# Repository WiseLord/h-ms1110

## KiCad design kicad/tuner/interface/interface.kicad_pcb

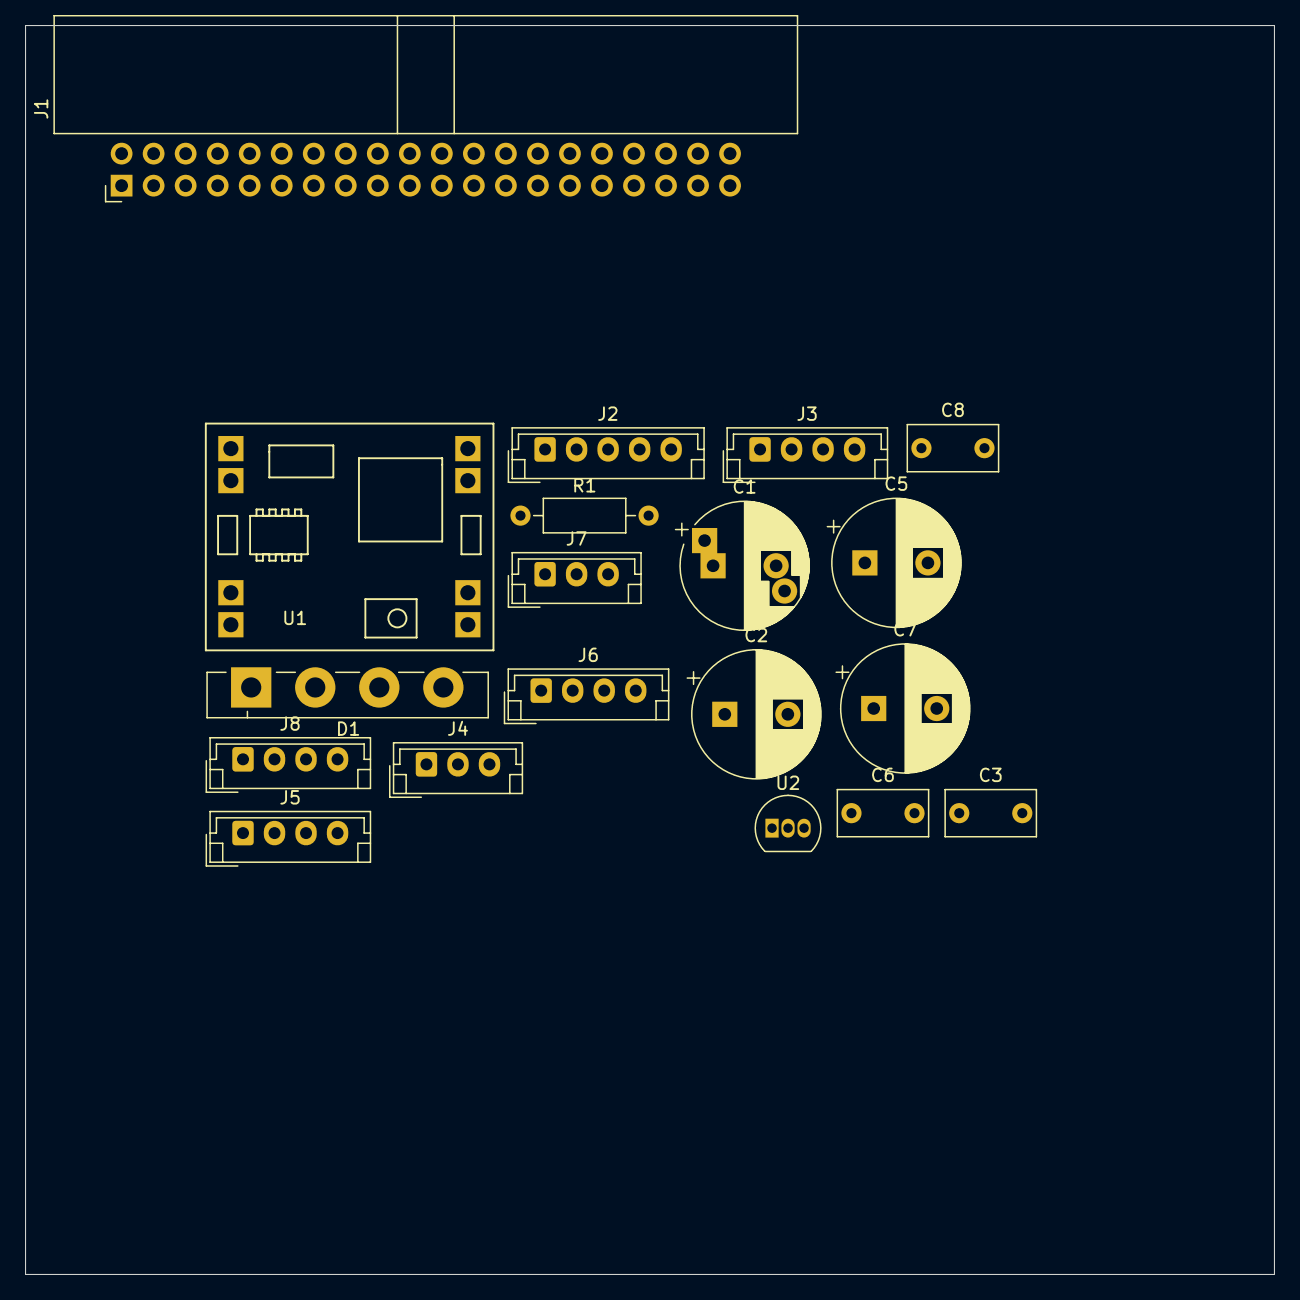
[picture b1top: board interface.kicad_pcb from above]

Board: 2 copper layers, 99.1 x 99.1 mm, 19 parts (0 on the bottom side), 22 nets, no tracks yet.

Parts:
C1: 1000.0; CP_Radial_D10.0mm_P5.00mm_P7.50mm
C2: 470.0; CP_Radial_D10.0mm_P5.00mm
C3, C6, C8: 0.1; C_Rect_L7.0mm_W3.5mm_P5.00mm
C5, C7: 220.0; CP_Radial_D10.0mm_P5.00mm
D1: GBU8K; Diode_Bridge_Vishay_GBU
J1: H-MS1110_Bus; IDC-Header_2x20_P2.54mm_Horizontal
J2: EXT_INPUT; JST_EH_B5B-EH-A_1x05_P2.50mm_Vertical
J3: SYNC; JST_EH_B4B-EH-A_1x04_P2.50mm_Vertical
J4: ROT; JST_EH_B3B-EH-A_1x03_P2.50mm_Vertical
J5: CONTROL; JST_EH_B4B-EH-A_1x04_P2.50mm_Vertical
J6: FP_POWER; JST_EH_B4B-EH-A_1x04_P2.50mm_Vertical
J7: SPECT; JST_EH_B3B-EH-A_1x03_P2.50mm_Vertical
J8: I2C; JST_EH_B4B-EH-A_1x04_P2.50mm_Vertical
R1: 100; R_Axial_DIN0207_L6.3mm_D2.5mm_P10.16mm_Horizontal
U1: MP1584EN_module
U2: L78L12_TO92; TO-92_Inline

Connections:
+5V: C2.1, C3.1, J6.1, J6.2, U1.7, U1.8
/+3.3VA: J1.9, J2.1
/AC1: D1.3, J1.17
/AC2: D1.2, J1.19
/AD1: J1.2, J2.3
/AD2: J1.1, J2.2
/AD3: J1.14, J2.4
/MUTE: J1.24, J5.1
/REMOTE: J1.15, J5.3
/ROT-A: J1.12, J4.3
/ROT-B: J1.10, J4.1
/SP_L: J1.27, J7.1
/SP_R: J1.34, J7.3
/STBY: J1.22, J5.2
/SYNC_DATA: J1.16, J3.2
/SYNC_SCK: J1.18, J3.3
GNDA: C5.2, C6.2, C7.2, C8.2, J1.25, J1.33, J1.35, J1.38, U2.2
GNDD: C1.2, C2.2, C3.2, D1.4, J1.11, J2.5, J3.4, J4.2, J5.4, J6.3, J6.4, J7.2, J8.4, U1.3, U1.4, U1.5, U1.6
unnamed: C1.1, D1.1, U1.1, U1.2
unnamed: C5.1, C6.1, R1.1, U2.3
unnamed: C7.1, C8.1, U2.1
unnamed: J1.32, R1.2

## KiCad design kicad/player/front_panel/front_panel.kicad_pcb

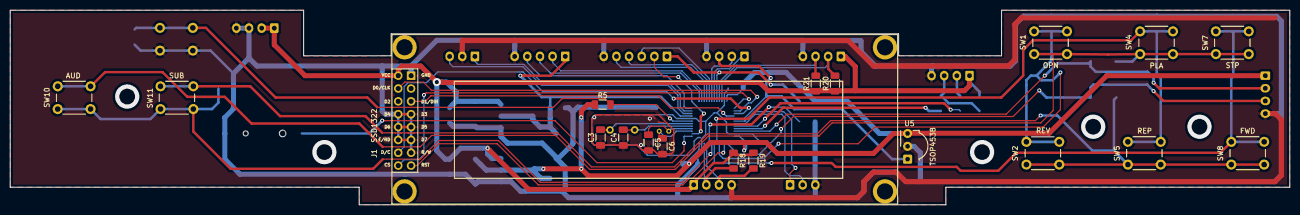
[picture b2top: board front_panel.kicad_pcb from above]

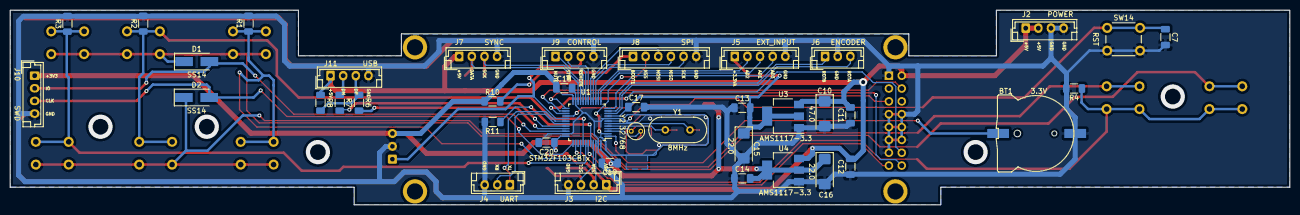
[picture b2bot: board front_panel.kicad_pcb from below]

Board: 2 copper layers, 253.0 x 38.5 mm, 59 parts (40 on the bottom side), 47 nets.

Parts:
BT1: 3.3V; CR1220
C3, C4: 20p; C_1206_3216Metric_Pad1.33x1.80mm_HandSolder
C5, C6: 6p2; C_1206_3216Metric_Pad1.33x1.80mm_HandSolder
C7: 100n; C_1206_3216Metric_Pad1.33x1.80mm_HandSolder
C10: 47.0; CP_EIA-6032-28_Kemet-C
C11, C12, C13, C14, C17, C18, C19, C20: 0.1; C_1206_3216Metric_Pad1.33x1.80mm_HandSolder
C15, C16: 22.0; CP_EIA-6032-28_Kemet-C
D1, D2: SS14; D_SMA_Handsoldering
J1: SSD1322; SSD1322_3.12
J2: POWER; JST_EH_B4B-EH-A_1x04_P2.50mm_Vertical
J3: I2C; JST_EH_B4B-EH-A_1x04_P2.50mm_Vertical
J4: UART; JST_EH_B3B-EH-A_1x03_P2.50mm_Vertical
J5: EXT_INPUT; JST_EH_B5B-EH-A_1x05_P2.50mm_Vertical
J6: ENCODER; JST_EH_B3B-EH-A_1x03_P2.50mm_Vertical
J7: SYNC; JST_EH_B4B-EH-A_1x04_P2.50mm_Vertical
J8: SPI; JST_EH_B6B-EH-A_1x06_P2.50mm_Vertical
J9: CONTROL; JST_EH_B4B-EH-A_1x04_P2.50mm_Vertical
J10: SWD; JST_EH_B4B-EH-A_1x04_P2.50mm_Vertical
J11: USB; JST_EH_B4B-EH-A_1x04_P2.50mm_Vertical
R1, R2, R3, R4: 33k; R_1206_3216Metric_Pad1.30x1.75mm_HandSolder
R5: 22k; R_1206_3216Metric_Pad1.30x1.75mm_HandSolder
R6, R7: 22; R_1206_3216Metric_Pad1.30x1.75mm_HandSolder
R8, R18, R19, R20, R21: 10k; R_1206_3216Metric_Pad1.30x1.75mm_HandSolder
R10, R11: 100k; R_1206_3216Metric_Pad1.30x1.75mm_HandSolder
SW1: OPN; SW_PUSH_6mm
SW2: REV; SW_PUSH_6mm
SW4: PLA; SW_PUSH_6mm
SW5: REP; SW_PUSH_6mm
SW7: STP; SW_PUSH_6mm
SW8: FWD; SW_PUSH_6mm
SW10: AUD; SW_PUSH_6mm
SW11: SUB; SW_PUSH_6mm
SW14: RST; SW_PUSH_6mm
U1: STM32F103CBTx; LQFP-48_7x7mm_P0.5mm
U3, U4: AMS1117-3.3; SOT-223-3_TabPin2
U5: TSOP4538; Vishay_MOLD-3Pin
Y1: 8MHz; Crystal_HC49-4H_Vertical
Y2: 32768; Crystal_C38-LF_D3.0mm_L8.0mm_Vertical

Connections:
+3.3VA: C13.2, C15.1, C17.1, J5.1, U1.9, U3.2
+3V3: C14.2, C16.1, C18.1, C19.1, C20.1, J10.1, R5.1, R10.1, U1.24, U1.36, U1.48, U4.2, U5.3
+5V: C10.1, C11.2, C12.2, J1.2, J2.1, J2.2, J3.1, J7.1, J11.1, R8.1, R18.1, R19.1, R20.1, R21.1, U3.3, U4.3
/AD1: J5.3, U1.13
/AD2: J5.2, U1.14
/AD3: J5.4, U1.12
/BOOT0: R11.1, U1.44
/BOOT1: J8.1, R10.2, U1.20
/DISP_CLK: J1.4, U1.26
/DISP_CS: J1.16, U1.25
/DISP_DC: J1.14, U1.27
/DISP_DIN: J1.5, U1.28
/DISP_RST: J1.15, U1.38
/DM: J11.2, R7.1
/DP: J11.3, R6.1, R8.2
/K1: R1.1, SW1.1, SW2.1, U1.40
/K2: R2.1, SW4.1, SW5.1, U1.41
/K3: R3.1, SW7.1, SW8.1, U1.42
/K4: R4.1, SW10.1, SW11.1, U1.43
/KS1: D1.1, SW1.2, SW4.2, SW7.2, SW10.2
/KS2: D2.1, SW2.2, SW5.2, SW8.2, SW11.2
/MUTE: J9.1, U1.19
/NRST: C7.1, R5.2, SW14.1, U1.7
/OSC32_IN: C6.1, U1.3, Y2.2
/OSC32_OUT: C5.1, U1.4, Y2.1
/OSC_IN: C4.2, U1.5, Y1.1
/OSC_OUT: C3.2, U1.6, Y1.2
/REMOTE: J9.3, U1.29, U5.1
/ROTA: J6.3, U1.10
/ROTB: J6.1, U1.11
/RX: J4.2, U1.31
/S1: D1.2, J10.2, U1.34
/S2: D2.2, J10.3, U1.37
/SCL: J3.3, R19.2, U1.45
/SDA: J3.2, R18.2, U1.46
/SPI_MISO: J8.4, U1.16
/SPI_MOSI: J8.3, U1.17
/SPI_NSS: J8.2, U1.2
/SPI_SCK: J8.5, U1.15
/STBY: J9.2, U1.18
/SYNC_DATA: J7.2, R20.2, U1.22
/SYNC_SCK: J7.3, R21.2, U1.21
/TX: J4.1, U1.30
/USB_DM: R7.2, U1.32
/USB_DP: R6.2, U1.33
/VBAT: BT1.1, U1.1
GNDD: BT1.2, C3.1, C4.1, C5.2, C6.2, C7.2, C10.2, C11.1, C12.1, C13.1, C14.1, C15.2, C16.2, C17.2, C18.2, C19.2, C20.2, J1.1, J1.7, J1.8, J1.9, J1.10, J1.11, J1.12, J1.13, J2.3, J2.4, J3.4, J4.3, J5.5, J6.2, J7.4, J8.6, J9.4, J10.4, J11.4, R1.2, R2.2, R3.2, R4.2, R11.2, SW14.2, U1.8, U1.23, U1.35, U1.47, U3.1, U4.1, U5.2

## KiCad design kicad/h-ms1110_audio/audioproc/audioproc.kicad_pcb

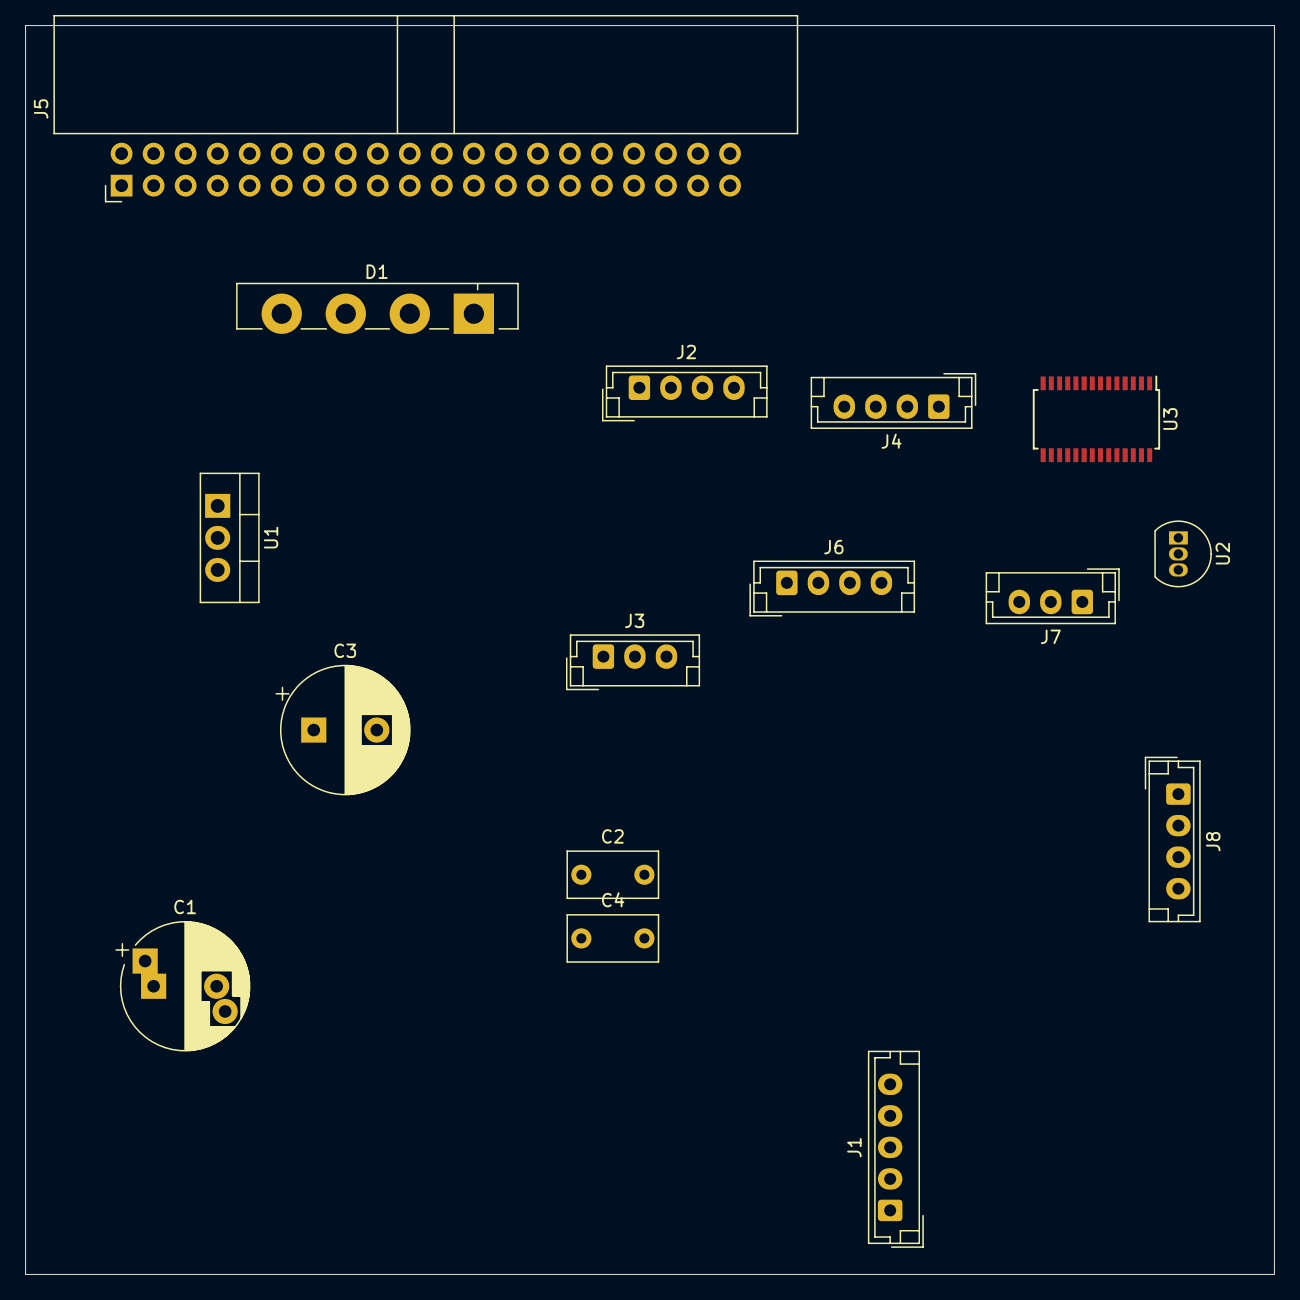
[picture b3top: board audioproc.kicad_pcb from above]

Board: 2 copper layers, 99.1 x 99.1 mm, 16 parts (0 on the bottom side), 27 nets, no tracks yet.

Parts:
C1: 4700.0; CP_Radial_D10.0mm_P5.00mm_P7.50mm
C2, C4: 0.1; C_Rect_L7.0mm_W3.5mm_P5.00mm
C3: 1000.0; CP_Radial_D10.0mm_P5.00mm
D1: GBU8K; Diode_Bridge_Vishay_GBU
J1: EXT_INPUT; JST_EH_B5B-EH-A_1x05_P2.50mm_Vertical
J2: SYNC; JST_EH_B4B-EH-A_1x04_P2.50mm_Vertical
J3: ROT; JST_EH_B3B-EH-A_1x03_P2.50mm_Vertical
J4: CONTROL; JST_EH_B4B-EH-A_1x04_P2.50mm_Vertical
J5: H-MS1110_Bus; IDC-Header_2x20_P2.54mm_Horizontal
J6: FP_POWER; JST_EH_B4B-EH-A_1x04_P2.50mm_Vertical
J7: AUDIO; JST_EH_B3B-EH-A_1x03_P2.50mm_Vertical
J8: I2C; JST_EH_B4B-EH-A_1x04_P2.50mm_Vertical
U1: LM7805_TO220; TO-220-3_Vertical
U2: L78L12_TO92; TO-92_Inline
U3: TDA7719; TSSOP-28_4.4x9.7mm_P0.65mm

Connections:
+5V: C3.1, C4.1, J6.1, J6.2, U1.3
/+3.3VA: J1.1, J5.9
/AC1: D1.3, J5.17
/AC2: D1.2, J5.19
/AD1: J1.3, J5.2
/AD2: J1.2, J5.1
/AD3: J1.4, J5.14
/MUTE: J4.1, J5.24
/OUT_L: J5.29, U3.21
/OUT_R: J5.30, U3.18
/REMOTE: J4.3, J5.15
/ROT-A: J3.3, J5.12
/ROT-B: J3.1, J5.10
/SCL: J8.3, U3.25
/SDA: J8.2, U3.26
/SP_L: J5.27, J7.1, U3.17
/SP_R: J5.34, J7.3, U3.16
/STBY: J4.2, J5.22
/SYNC_DATA: J2.2, J5.16
/SYNC_SCK: J2.3, J5.18
/TUN-L: J5.39, U3.1
/TUN-R: J5.40, U3.2
GNDA: J5.25, J5.33, J5.35, J5.38, U2.2, U3.15
GNDD: C1.2, C2.2, C3.2, C4.2, D1.4, J1.5, J2.4, J3.2, J4.4, J5.11, J6.3, J6.4, J7.2, J8.4, U1.2
unnamed: C1.1, C2.1, D1.1, U1.1
unnamed: J5.32, U2.3
unnamed: U2.1, U3.24

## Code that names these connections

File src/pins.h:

#ifndef PINS_H
#define PINS_H

#ifdef __cplusplus
extern "C" {
#endif

#include <stdbool.h>
#include <stdint.h>

#include "hwlibs.h"

#define CONCAT(x,y)             x ## y

#define SET(p)                  (LL_GPIO_SetOutputPin(CONCAT(p, _Port), CONCAT(p, _Pin)))
#define CLR(p)                  (LL_GPIO_ResetOutputPin(CONCAT(p, _Port), CONCAT(p, _Pin)))

#define READ(p)                 (LL_GPIO_ReadInputPort(CONCAT(p, _Port)) & (CONCAT(p, _Pin) >> GPIO_PIN_MASK_POS) & 0x0000FFFFU)

// TFT parallel (8-bit) wiring
#define DISP_CS_Port            GPIOB
#define DISP_CS_Pin             LL_GPIO_PIN_12
#define DISP_RS_Port            GPIOB
#define DISP_RS_Pin             LL_GPIO_PIN_14  // SPI DC
#define DISP_RST_Port           GPIOA
#define DISP_RST_Pin            LL_GPIO_PIN_15

#define STBY_Port               GPIOB
#define STBY_Pin                LL_GPIO_PIN_0
#define MUTE_Port               GPIOB
#define MUTE_Pin                LL_GPIO_PIN_1

#define AIN_BTN_Port            GPIOA
#define AIN_BTN_Pin             LL_GPIO_PIN_4
#define AIN_BTN_ADC_Channel     LL_ADC_CHANNEL_4
#define AIN_POT_A_Port          GPIOA
#define AIN_POT_A_Pin           LL_GPIO_PIN_2
#define AIN_POT_A_Channel       LL_ADC_CHANNEL_2
#define AIN_POT_B_Port          GPIOA
#define AIN_POT_B_Pin           LL_GPIO_PIN_3
#define AIN_POT_B_Channel       LL_ADC_CHANNEL_3

#define ENCODER_Port            GPIOA
#define ENCODER_A_Pin           LL_GPIO_PIN_11
#define ENCODER_B_Pin           LL_GPIO_PIN_12

// Remote control pins
#define RC_Port                 GPIOA
#define RC_Pin                  LL_GPIO_PIN_8
#define RC_ExtiLine             LL_EXTI_LINE_8
#define RC_AR_ExtiPort          LL_GPIO_AF_EXTI_PORTA
#define RC_AR_ExtiLine          LL_GPIO_AF_EXTI_LINE8

void pinsInit(void);

#ifdef __cplusplus
}
#endif

#endif // PINS_H

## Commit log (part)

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2019-12-10 Schematic and initial PCB
2019-12-11 Initial SSD1322-ready code based on wl_lcd-f103
2019-12-11 Basic analog input reading
2019-12-14 KiCad: Move front_panel project to subdir
2019-12-15 Remove unused stuff
2019-12-15 Use colors of 4-bit grayscale
2019-12-15 Sync graphic library with ampcontrol/wl_lcd
2019-12-17 Use memory functions from stdlib
2020-01-07 Sync with ampcontrol-f103
2020-01-07 Improve SSD1322 code
2020-01-07 SSD1322 rotate support
2020-01-08 Add base amp file
2020-01-08 Basic drawing skeleton
2020-01-08 Input timer
2020-01-08 Draw pot values
2020-01-10 Move potentiometer calculations to input module
2020-01-10 Fixes for potentiometer calculations
2020-01-11 Sync code with other projects
2020-01-11 Add analog buttons support
2020-01-11 Added some code from ampcontrol project
2020-01-11 Basic ON/OFF control
2020-01-12 Separate screen module
2020-01-12 Change to STM32F103CB in Kicad project
2020-01-12 Fix analog buttons
2020-01-12 Rotary encoder support
2020-01-16 Cleanum makefile
2020-01-17 Add basic schematic for audioproc module
2020-01-18 Basic audio support
2020-01-18 Basic input indication
2020-01-19 Small rework of audio API
2020-01-19 Rid potentiometer grid from audio params
2020-01-19 Sync audio code with ampcontrol
2020-01-19 Improve potentiometer accuracy
2020-01-19 Control bass/treble via potentiometers
2020-01-19 Add menu files
2020-01-19 Basic menu drawing
2020-01-20 Layout and palette support from ampcontrol
2020-01-20 Improve handling potentiometers
2020-01-21 Schematics update
2020-01-21 Basic menu navigation
2020-01-23 Remote control support
2020-01-25 Audioproc schematic update
2020-02-01 Refactored colors
2020-02-02 Add handler for USART1 interrupt
2020-02-25 Fix flash definitions
2020-03-08 Matrix keyboard support
2020-03-08 Enable SWD interface in standby mode
2020-03-09 Spectrum draft from ampcontrol project
2020-03-09 Update schematcis and PCB
2020-03-10 Some work on spectrum settings
2020-03-10 LTO support, currently disabled
2020-03-11 Draw time
2020-03-14 Sync spectrum code with ampcontrol
2020-03-14 Move project files outside src directory
2020-03-14 Reset silence timer on signal
2020-03-14 Reduce display current
2020-03-14 Small fix in sch
2020-03-14 Remove junk SSD1322 scroll defines
2020-03-18 Split audio and tuner code
2020-03-21 Sync and cleanup audio code
2020-03-21 Move audio and tuner code to common dir
2020-03-22 Pass STANDBY to tuner
2020-03-22 Introduce sync structures
2020-03-22 Pass actions from tuner to audio
2020-03-22 Common input module for both audio and tuner
2020-03-23 Use common layout for tuner and audio
2020-03-23 Common canvas for both audio and tuner
2020-03-24 Refactor showStandby
2020-03-24 Adjust some SSD1322 brightness-related params
2020-03-25 Fix spectrum drawing
2020-03-25 Separate schematic for audio and tuner front panels
2020-03-27 Update audioproc schematic
2020-03-28 Add MP1584 module symbols
2020-03-28 Add player block schematics
2020-04-02 Bigger fonts for date and time
2020-04-04 Remove separate canvases
2020-04-04 Separate matrix input library
2020-04-04 Separate analog input library
2020-04-05 Rework player schematics
2020-04-06 Player board skeleton
2020-04-08 Player board: mcu part
2020-04-08 Autorouted player front panel PCB
2020-04-19 Finished player board
2020-04-23 Some simplifications in canvas
2020-04-23 Separate spectrum drawing
2020-04-23 Change sp defaul settings
2020-04-24 Refactor spectrum view
2020-04-24 Simplify layout
2020-04-24 Refactored widgets, added paramview one
2020-04-26 Refactored tune
2020-04-26 Refactored screen
2020-04-26 Refactored amp
2020-04-26 Refactor project files
2020-04-26 Refactored palette
2020-04-26 Refactor actions
2020-04-26 Draw volume progressbar
2020-04-27 Show current input
2020-04-27 Handling analog input
2020-04-28 Separate project files
2020-04-28 Refactor eemul and settings
2020-04-28 Map display buttons
2020-04-28 Pass all buttons from tuner
2020-04-28 Rework pass buttons and encoder
2020-04-28 Sync time
2020-04-29 Date and time screens
2020-04-30 Fix volume restoring
2020-04-30 Sync with ampcontrol project
2020-04-30 Add setup action and screen skeleton
2020-05-01 Remove layout
2020-05-02 Refactored screens
2020-05-02 Proper SWD handling
2020-05-02 Date/time setup implemented
2020-05-02 Get rid of utilMkStr()
2020-05-02 Add time and date views
2020-05-02 Remove MUTE/STBY in tuner
2020-05-02 Some fixes
2020-05-03 Implement alarm setup
2020-05-03 Remote setup
2020-05-03 Fix setup navigation
2020-05-04 Sync spectrum mode
2020-05-05 Rename KiCad projects
2020-05-05 Add useconds delay function
2020-05-05 Add tuner interface board skeleton
2020-05-09 Initial LC7213X PLL support
2020-05-10 Basic FM screen
2020-05-10 Basic radio tuning
2020-05-11 Fix tuner freq after power off
2020-05-11 Add registers for LC7213X
2020-05-11 LC7213X improvements
2020-05-17 Rework pins
2020-05-29 Prepare slave data to transmit earlier
2020-05-29 Rework and optimize master-to-slave sync
2020-05-29 Rework and optimize slave-to-master sync
2020-05-30 Sync display code with ampcontrol
2020-06-06 Add player subproject
2020-06-06 Rework some sync structs
2020-06-06 Sync player support
2020-07-09 Weekday draw in player module
2020-08-20 Rework audio module to be main block
2020-08-21 Rename projects
2020-08-21 Show spectrum in spectrum module
2020-08-22 Fix tuneview in player
2020-09-06 Sync display code
2020-09-13 Sync with latest GLCD library
2020-09-13 Small refactoring
2020-09-14 Refactor inType
2020-09-15 Refactor handle SWD function
2020-09-17 Amp struct unification
2020-09-17 Fix unused input label
2020-09-17 Fix input screen timeout
2020-09-22 Rearrange actions and make remote volume buttons work
2020-09-22 Audio mute support. Screen implementation required
2020-11-01 Refactored project
2020-11-01 Station storing
2020-11-03 Added fav stations support
2020-11-08 Support station detect
2020-11-12 Draw PT2579 tuner schematic part
2020-11-16 Update interfaces schematics
2020-11-18 Enable TDA7719 subwoofer channels
2020-11-18 Make TDA7719 able to use 2.0, 2.1, 4.0, 4.1 modes
2020-11-18 Function to check for supported audio mode
2020-11-18 Enable LP filter in sub modes for TDA7719
2020-11-20 Improve subwoofer gain on TDA7719
2020-12-03 Basic work with mpd-uart.py
2020-12-03 Rename audio inputs
2020-12-03 Better MPD control
2020-12-03 mpd-uart systemd service
2020-12-03 Fix crash
2020-12-04 Icons support
2020-12-04 Update MPD icon
2020-12-04 Elapsed time periodic passing
2020-12-04 Scroll song name support
2020-12-05 Increase MPD drawing performance
2020-12-05 Add play/pause/stop icons support
2020-12-05 Update schematics
2020-12-06 MPC: add more status icons
2020-12-06 Add MPD status control
2020-12-06 Project refactoring
2020-12-07 Add InputView
2020-12-07 Add AUX icons
2020-12-07 Update mpd-uart scripts
2020-12-07 Small input refactoring
2020-12-07 Refactored input actions
2020-12-07 Small handlers refactoring
2020-12-07 Refactored settings
2020-12-07 Fix broken RC and tuner
2020-12-07 Add more RC buttons to recognize
2020-12-08 Sync refactoring
2020-12-08 Basic tuner sync
2020-12-08 More tuner sync parameters
2020-12-08 Request tuner on player start
2020-12-08 Add tuner icons
2020-12-09 Refactored projects
2020-12-09 Common amp file
2020-12-09 Get buttons and encoders in common amp
2020-12-11 Fix build error if LC7213X is not selected
2020-12-12 Sync tuner code with ampcontrol
2020-12-13 Refactored tuner parser
2020-12-13 Simple RDS demod implementation
2020-12-13 RDS demod through buffer with correction
2020-12-18 Update player schematcis
2020-12-18 IconImage widget
2020-12-19 Refactored widgets
2020-12-19 Add scrolltext widget
2020-12-19 Use TunerView to draw radio
2020-12-19 Refactoring tunerView
2020-12-19 Refactored player positioning
2020-12-19 Sync RDS
2020-12-19 Add SPDIF icon
2020-12-20 RDS flag handling in tuner
2020-12-20 Simplify RDS sync
2020-12-20 RDS lost handling
2020-12-21 Stations store/clear support
2020-12-22 Draw station num
2020-12-23 Use tuner encoder as REW/FFWD in MPD
2020-12-24 Refactoring amp
2020-12-24 Improve RDS parser
2021-01-29 Sync MPC module with ampcontrol
2021-01-29 Don't sync with slaves if they are not online
2021-01-30 Support brightnes control for SSD1322
2021-01-30 Reworking time output
2021-01-30 Common project for all modules
2021-01-30 Combine project files
2021-01-30 Rework sp modes, add peaks toggle button
2021-01-31 Remove ssd1322.h
2021-01-31 SSD1322 init rework
2021-01-31 Demo screensaver support
2021-01-31 Refactored demo into starsview
2021-02-06 Refactored demo
2021-02-11 PCM5102 RPi connection schematic
2021-02-11 Refactored timers
2021-02-11 Rework spectrum flags
2021-02-11 Refactor spectrum init
2021-02-13 Improve sync
2021-02-16 Unify makefiles
2021-02-16 Simplify project structure
2021-02-16 Unify source files
2021-02-22 MPD-uart: update IP in background
2021-02-23 Detect slaves connection and disconnection
2021-02-24 Tuner and spectrum modules hotplug
2021-02-24 Fix partial spectrum drawing
2021-02-24 Fix tuner view
2021-02-24 Support RDS and MONO tuner switches
2021-02-24 Fix ffwd/rewind actions from tuner
2021-02-28 MPD poweroff feature
2021-02-28 Fix command parse exception
2021-03-01 Reduce RPi poweroff timeout
2021-03-02 Sync stars view with ampcontrol
2021-03-02 Make demo smoother
2021-03-02 Update interface schematics
2021-03-02 Fix alarm work
2021-03-02 Sync display driver with ampcontrol
2021-03-02 Skip unused input
2021-03-19 Add RPi-related files
2021-03-19 Add BananaPi zero PC5102 variant
2021-03-25 Input control rework
2021-03-25 Add scroll timer for input selector
2021-03-25 Add input selector scrolling
2021-03-26 Fix some tunes
2021-03-26 Update CMSIS
2021-03-26 Partial setup refactoring
2021-03-27 Less noise-sensitive spectrum
2021-03-27 Update player interface schematic
2021-03-27 Refactored tuner status flags
2021-03-27 Refactored tuner
2021-03-28 Update schematics - use more GNDD lines
2021-03-28 Additional TDA7719 tunes support
2021-03-28 Better audio params tuning
2021-03-29 Optimize audio tunes
2021-03-29 Add mute screen
2021-03-29 RC and other improvements
2021-03-29 Fix IP on MPD/KaRadio
2021-03-29 Add scroll left-right factor
2021-03-30 Sync RTC code
2021-03-30 Switch band button to select between FM and MPD/Radio
2021-03-31 Show stars screen on silence
2021-03-31 Show input selector on start
2021-03-31 Rework spGetDb function
2021-04-01 Add control of BT on Raspberry PI
2021-04-03 Change Bluetooth init
2021-04-05 Improve MPD/BT mode detection
2021-04-05 Less threshold for signal detection
2021-04-05 Audio fixes from ampcontrol
2021-04-05 Add BT mode switch via remote
2021-04-06 Fix meta on MPD mode change
2021-06-12 Move syncAction to ampPriv struct
2021-06-12 Filter actions on slaves in standby mode
2021-06-14 Modify schematic regarding MPD power control
2021-06-15 Get rid of sscanf
2021-06-22 Show common input icon
2021-06-23 Add RTC correction settings
2021-06-24 Optimize settings storing
2021-07-09 Audio getInCnt API function
2021-07-09 TDA7719: support input configurations
2021-07-09 Switch to IN_CFG_5
2021-07-25 Sync with latest glcd driver
2021-08-20 Enable control via USB
2021-08-22 Move spectrumview code
2021-08-22 Spectrum code simplify
2021-08-22 Simplify datetime
2021-08-22 Move setupview
2022-02-19 Power off MPD more correct
2024-02-15 Move amp front panel to Kicad 6
2024-02-15 Move common front panel to Kicad 6
2024-02-15 Move pcm5102 to Kicad 6
2024-06-01 Increas I2C timeout
    This fixes hanging PLAYER module in case station saved/erased
2024-06-01 Handle ditit buttons on remote
2024-06-01 Update amp front_panel to Kicad 7
2024-06-01 Update common front_panel to Kicad 7
2024-06-01 Update pcm5102 to Kicad 7
2024-06-01 Update player interface to Kicad 7
2024-06-01 Update spectrum front_panel to Kicad 7
2024-06-01 Update spectrum interface to Kicad 7
2024-06-01 Update tuner front_panel to Kicad 7
2024-06-01 Update tuner interface to Kicad 7
2025-01-25 Support PLAY/STBY and STOP/STBY remote sequences
    Previously, if STBY button on remote was pressed, device switched
    between standby and active modes. There was no way to turn it on
    from or turn it off by separate commands.
    Now, fast (<200 ms) sequence of PLAY/STBY turns the device on (even
    if it was on before) while sequence of STOP/STBY turns it off.
    This can be used to guarantee the state when controlled from
